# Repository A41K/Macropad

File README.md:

# A41K's AIO (All in one) Macropad

This is my little submission for my Hackpad/Macropad I made

(Sorry for it looking a little weird)

# The Challenges
Honestly, the real challenge was learning Fusion360 (never used it before) and learning KiCad again. The most pain I had was with the wiring in
KiCad and the making of the top part of the Pad. These both took me atleast an hour, but the explanations really helped me to understand
what my problems were and how to fix them

# BOM
    6x Cherry MX Switches
    3x SK6812 MINI Leds
    1x XIAO RP2040
    6x Blank DSA Keycaps
    4x M3x16 Bolt
    4x M3 Heatset
    (Also a soldering iron because i dont have one 💀😭)

# Others:
- KMK Firmware
- Macropad-top.stl 
- Macropad-bottom.stl

# The Pad

Schematic            |  PCB         |   Case
:-------------------------:|:-------------------------:|:-------------------------:|
  |   |   |  

# My Experience (With a Picture and Video)
 | https://github.com/user-attachments/assets/34d5ca46-1c15-4404-9881-5d161b442853

It was honestly really fun and learnfull assembling the macropad. It was straightforward and easy (expect the soldering). 
As somebody who never soldered, never wired, never built a macropad or even 
built a PCB it was really easy and it led me to now building more and soldering/tinkering even more. 
It made me really interested in PCB's and how they work. I really loved this and I hope there will
be more kinds of projects like this

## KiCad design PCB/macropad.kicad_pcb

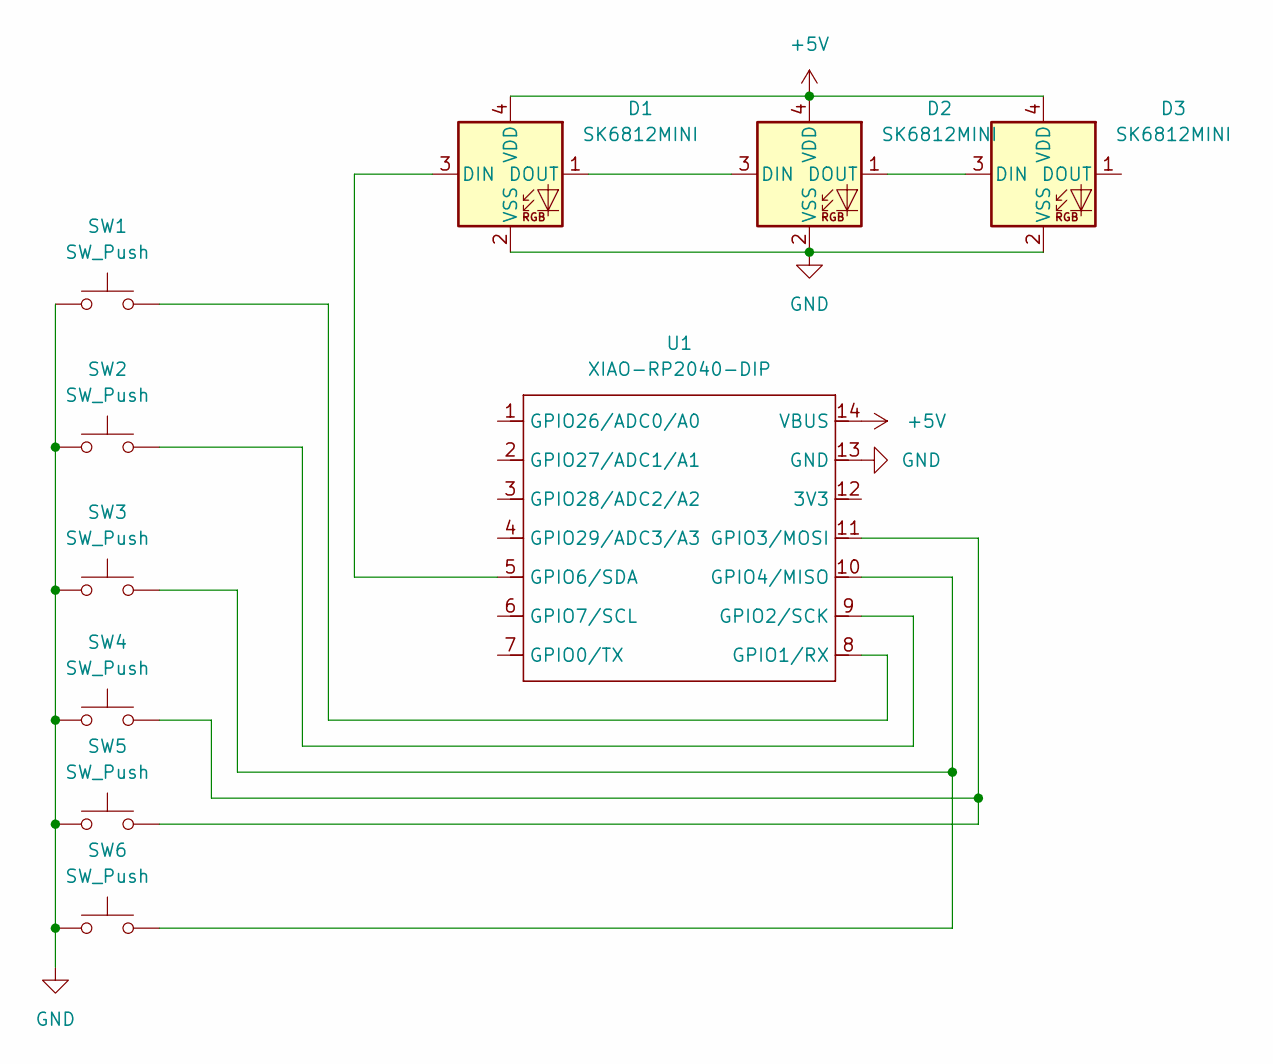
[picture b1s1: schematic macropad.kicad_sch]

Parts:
D1, D2, D3: SK6812MINI; LED_SK6812MINI_PLCC4_3.5x3.5mm_P1.75mm
SW1, SW2, SW3, SW4, SW5, SW6: SW_Push; SW_Cherry_MX_1.00u_PCB
U1: XIAO-RP2040-DIP

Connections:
+5V: D1.4 (VDD), D2.4 (VDD), D3.4 (VDD), U1.14 (VBUS)
GND: D1.2 (VSS), D2.2 (VSS), D3.2 (VSS), SW1.1, SW2.1, SW3.1, SW4.1, SW5.1, SW6.1, U1.13 (GND)
unnamed: D1.3 (DIN), U1.5 (GPIO6/SDA)
unnamed: D1.1 (DOUT), D2.3 (DIN)
unnamed: D2.1 (DOUT), D3.3 (DIN)
unnamed: SW1.2, U1.8 (GPIO1/RX)
unnamed: SW2.2, U1.9 (GPIO2/SCK)
unnamed: SW4.2, SW5.2, U1.11 (GPIO3/MOSI)
unnamed: SW3.2, SW6.2, U1.10 (GPIO4/MISO)

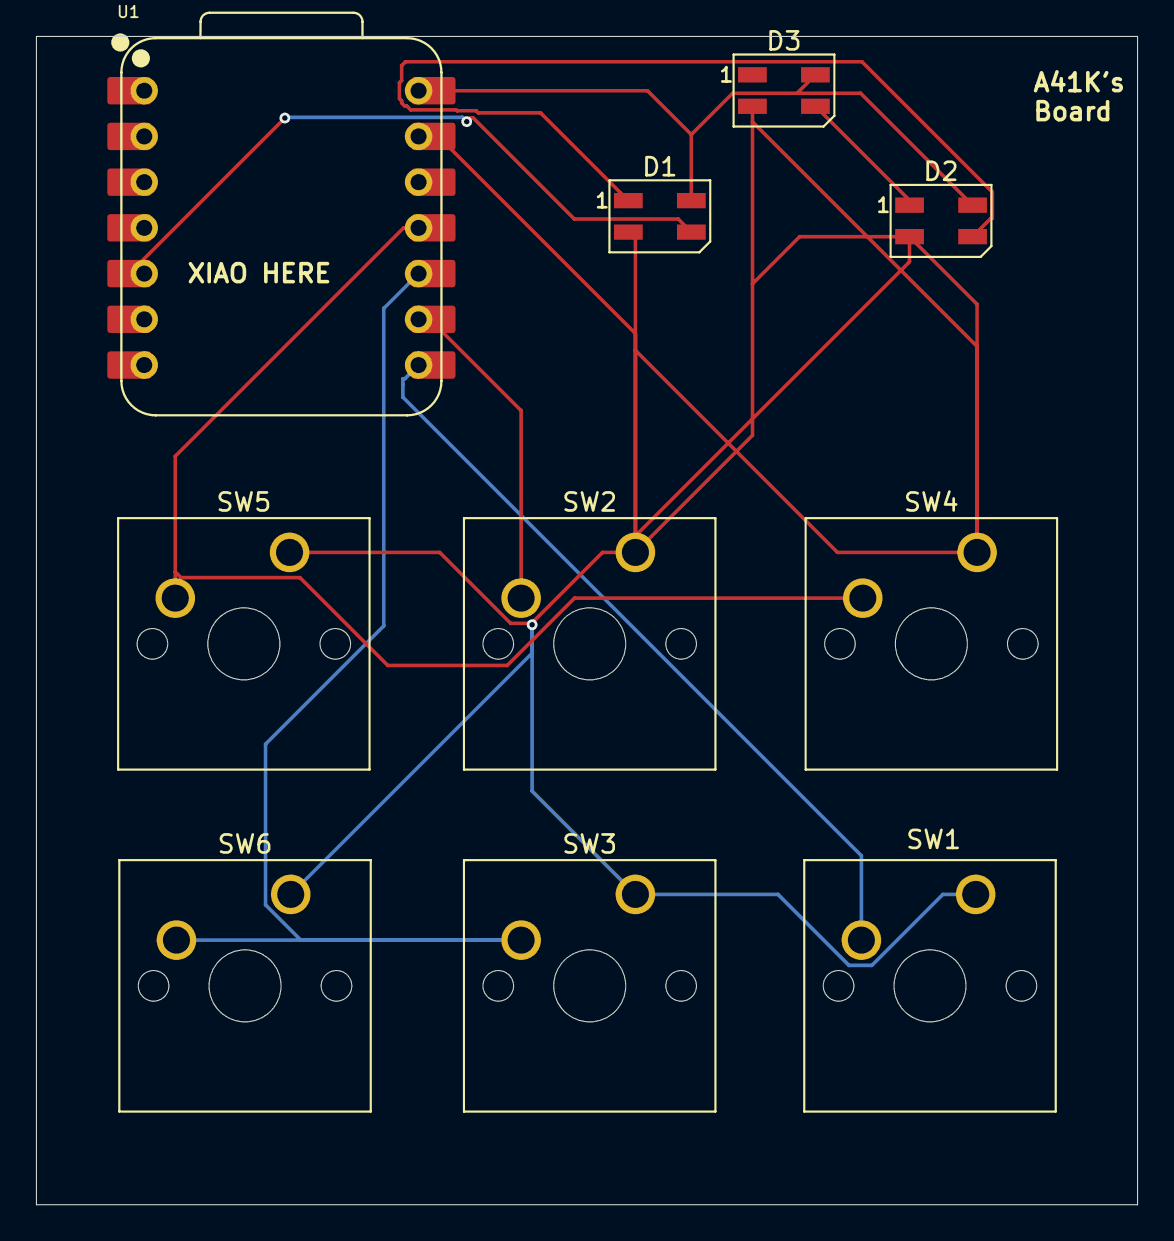
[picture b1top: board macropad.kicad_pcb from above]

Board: 2 copper layers, 61.2 x 64.9 mm, 10 parts (0 on the bottom side), 9 nets.

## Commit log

2025-12-02 PCB, CAD push
2025-12-02 Readme Push
2025-12-02 README fix
2025-12-02 Pushing another CAD
2025-12-02 Added Firmware And maybe finished
2026-02-05 Enhance README with experience and media
    Added personal experience section with images and video link.
